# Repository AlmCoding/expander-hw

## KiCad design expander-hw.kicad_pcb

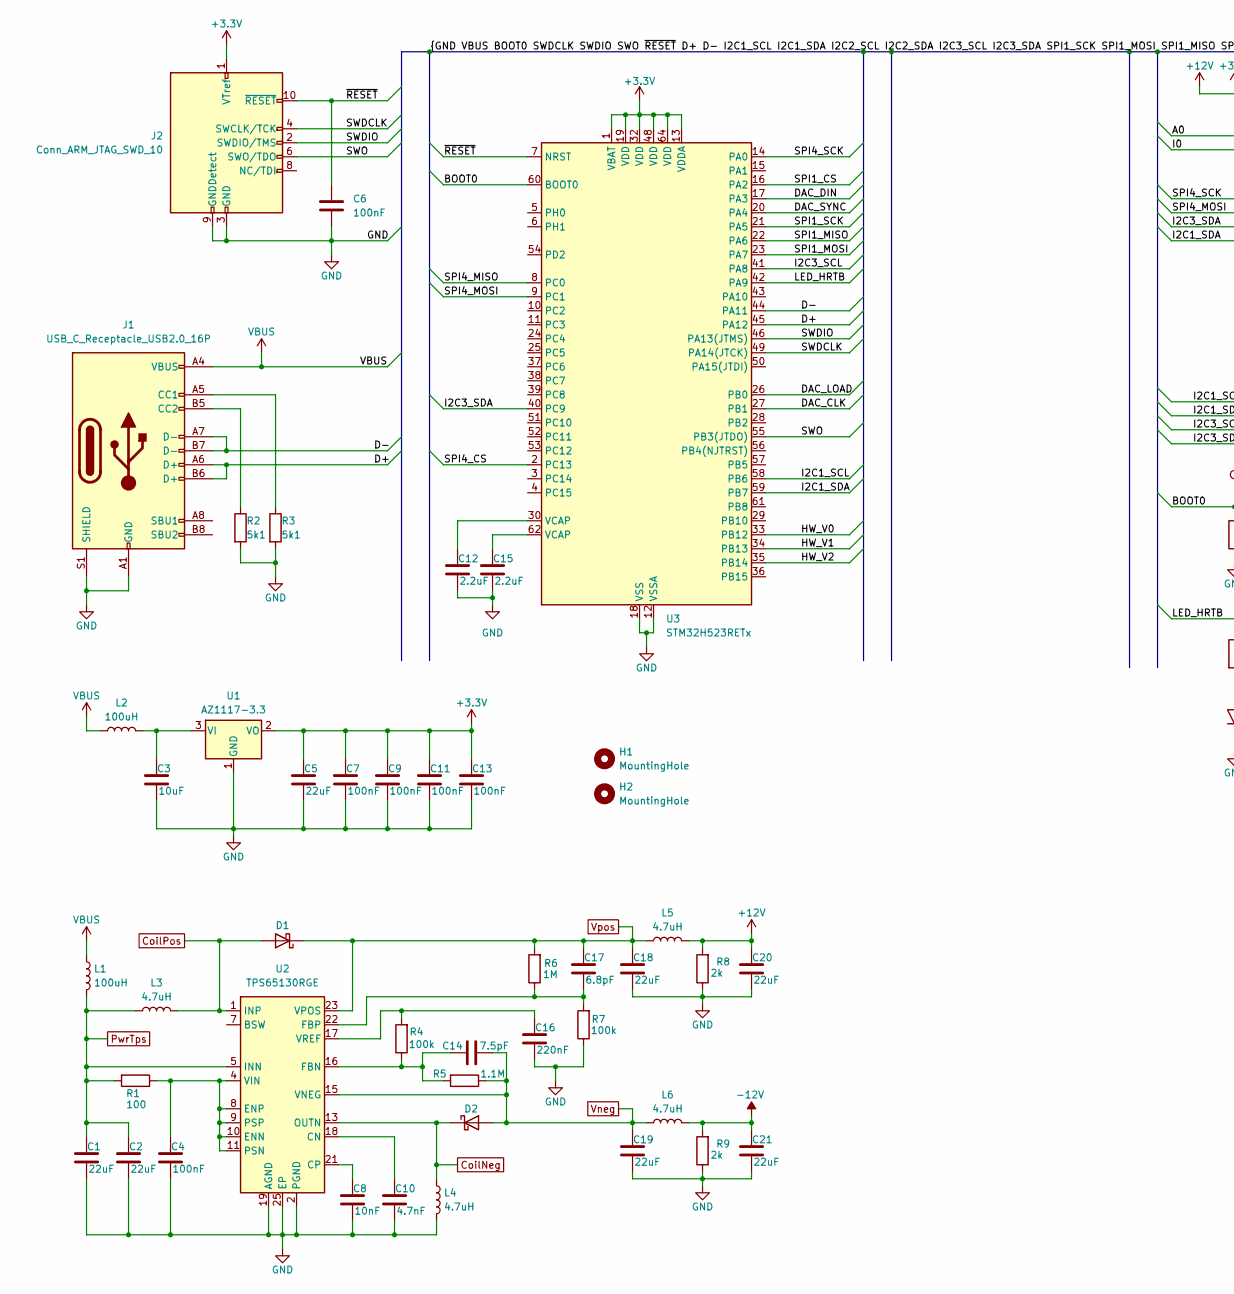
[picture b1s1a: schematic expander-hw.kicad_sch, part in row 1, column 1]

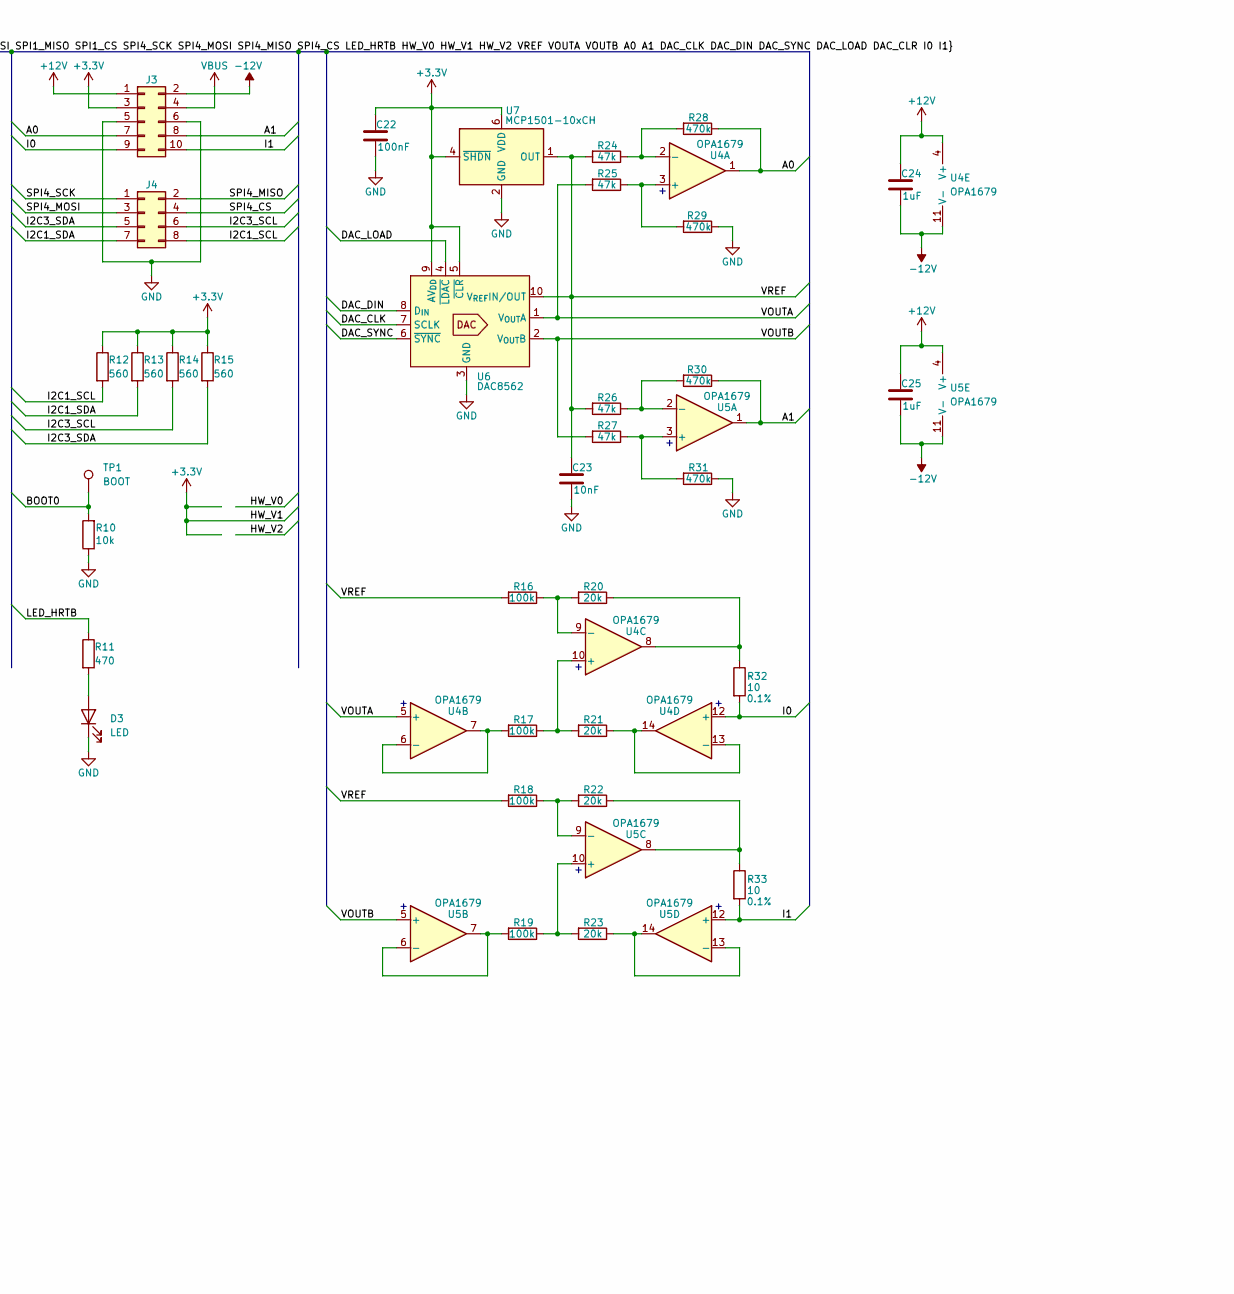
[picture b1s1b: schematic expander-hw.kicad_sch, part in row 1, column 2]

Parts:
C1, C2, C5, C18, C19, C20, C21: 22uF; C_0805_2012Metric
C3: 10uF; C_0805_2012Metric
C4, C6, C7, C9, C11, C13, C22: 100nF; C_0603_1608Metric
C8, C23: 10nF; C_0603_1608Metric
C10: 4.7nF; C_0603_1608Metric
C12, C15: 2.2uF; C_0603_1608Metric
C14: 7.5pF; C_0603_1608Metric
C16: 220nF; C_0603_1608Metric
C17: 6.8pF; C_0603_1608Metric
C24, C25: 1uF; C_0603_1608Metric
D1, D2: D_Schottky; D_0805_2012Metric
D3: LED; LED_0603_1608Metric
H1, H2: MountingHole; MountingHole_3.2mm_M3
J1: USB_C_Receptacle_USB2.0_16P; USB_C_Receptacle_G-Switch_GT-USB-7010ASV
J2: Conn_ARM_JTAG_SWD_10; PinHeader_2x05_P1.27mm_Vertical
J3: Conn_02x05_Odd_Even; PinHeader_2x05_P2.54mm_Horizontal
J4: Conn_02x04_Odd_Even; PinHeader_2x04_P2.54mm_Horizontal
L1, L2: 100uH; L_1210_3225Metric
L3, L4, L5, L6: 4.7uH; L_1210_3225Metric
R1: 100; R_0603_1608Metric
R2, R3: 5k1; R_0603_1608Metric
R4, R7, R16, R17, R18, R19: 100k; R_0603_1608Metric
R5: 1.1M; R_0603_1608Metric
R6: 1M; R_0603_1608Metric
R8, R9: 2k; R_0805_2012Metric
R10: 10k; R_0603_1608Metric
R11: 470; R_0603_1608Metric
R12, R13, R14, R15: 560; R_0603_1608Metric
R20, R21, R22, R23: 20k; R_0603_1608Metric
R24, R25, R26, R27: 47k; R_0603_1608Metric
R28, R29, R30, R31: 470k; R_0603_1608Metric
R32, R33: 10; R_0603_1608Metric; Tolerance 0.1%
TP1: BOOT; TestPoint_Pad_D2.5mm
U1: AZ1117-3.3; SOT-223-3_TabPin2
U2: TPS65130RGE; VQFN-24-1EP_4x4mm_P0.5mm_EP2.45x2.45mm_ThermalVias
U3: STM32H523RETx; LQFP-64_10x10mm_P0.5mm
U4, U5: OPA1679; SOIC-14_3.9x8.7mm_P1.27mm
U6: DAC8562; VSSOP-10_3x3mm_P0.5mm
U7: MCP1501-10xCH; SOT-23-6

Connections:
+3.3V: C5.1, C7.1, C9.1, C11.1, C13.1, C22.1, J2.1 (VTref), J3.3, R12.1, R13.1, R14.1, R15.1, U1.2 (VO), U3.1 (VBAT), U3.13 (VDDA), U3.19 (VDD), U3.32 (VDD), U3.34 (PB13), U3.48 (VDD), U3.64 (VDD), U6.5 (~CLR), U6.9 (AV_{DD}), U7.4 (~SHDN), U7.6 (VDD)
+12V: C20.1, C24.1, C25.1, J3.1, L5.2, R8.2, U4.4 (V+), U5.4 (V+)
-12V: C21.1, C24.2, C25.2, J3.2, L6.2, R9.2, U4.11 (V-), U5.11 (V-)
/A0: J3.7, R28.1, U4.1
/A1: J3.8, R30.1, U5.1
/BOOT0: R10.2, TP1.1, U3.60 (BOOT0)
/D+: J1.A6 (D+), J1.B6 (D+), U3.45 (PA12)
/D-: J1.A7 (D-), J1.B7 (D-), U3.44 (PA11)
/DAC_CLK: U3.27 (PB1), U6.7 (SCLK)
/DAC_DIN: U3.17 (PA3), U6.8 (D_{IN})
/DAC_LOAD: U3.26 (PB0), U6.4 (~LDAC)
/DAC_SYNC: U3.20 (PA4), U6.6 (~SYNC)
/HW_V0: U3.33 (PB12)
/HW_V2: U3.35 (PB14)
/I0: J3.9, R32.2, U4.12 (+)
/I1: J3.10, R33.2, U5.12 (+)
/I2C1_SCL: J4.8, R12.2, U3.58 (PB6)
/I2C1_SDA: J4.7, R13.2, U3.59 (PB7)
/I2C3_SCL: J4.6, R14.2, U3.41 (PA8)
/I2C3_SDA: J4.5, R15.2, U3.40 (PC9)
/LED_HRTB: R11.1, U3.42 (PA9)
/SPI1_CS: U3.16 (PA2)
/SPI1_MISO: U3.22 (PA6)
/SPI1_MOSI: U3.23 (PA7)
/SPI1_SCK: U3.21 (PA5)
/SPI4_CS: J4.4, U3.2 (PC13)
/SPI4_MISO: J4.2, U3.8 (PC0)
/SPI4_MOSI: J4.3, U3.9 (PC1)
/SPI4_SCK: J4.1, U3.14 (PA0)
/SWDCLK: J2.4 (SWCLK/TCK), U3.49 (PA14(JTCK))
/SWDIO: J2.2 (SWDIO/TMS), U3.46 (PA13(JTMS))
/SWO: J2.6 (SWO/TDO), U3.55 (PB3(JTDO))
/VOUTA: R25.2, U4.5 (+), U6.1 (V_{OUT}A)
/VOUTB: R27.2, U5.5 (+), U6.2 (V_{OUT}B)
/VREF: C23.1, R16.2, R18.2, R24.2, R26.2, U6.10 (V_{REF}IN/OUT), U7.1 (OUT)
/~RESET: C6.1, J2.10 (~RESET), U3.7 (NRST)
CoilNeg: D2.1 (K), L4.1, U2.13 (OUTN), U2.14 (OUTN)
CoilPos: D1.2 (A), L3.2, U2.1 (INP), U2.24 (INP)
GND: C1.2, C2.2, C3.2, C4.2, C5.2, C6.2, C7.2, C8.2, C9.2, C10.2, C11.2, C12.2, C13.2, C15.2, C16.2, C18.2, C19.2, C20.2, C21.2, C22.2, C23.2, D3.1 (K), J1.A1 (GND), J1.A12 (GND), J1.B1 (GND), J1.B12 (GND), J1.S1 (SHIELD), J2.3 (GND), J2.5 (GND), J2.9 (GNDDetect), J3.5, J3.6, L4.2, R2.2, R3.2, R7.1, R8.1, R9.1, R10.1, R29.1, R31.1, U1.1 (GND), U2.2 (PGND), U2.3 (PGND), U2.19 (AGND), U2.25 (EP), U3.12 (VSSA), U3.18 (VSS), U3.31 (VSS), U3.47 (VSS), U3.63 (VSS), U6.3 (GND), U7.2 (GND), U7.3 (GND), U7.5 (GND)
unnamed: C12.1, U3.30 (VCAP)
unnamed: C15.1, U3.62 (VCAP)
unnamed: D3.2 (A), R11.2
unnamed: J1.A5 (CC1), R3.1
unnamed: J1.B5 (CC2), R2.1
unnamed: R20.1, R32.1, U4.8
unnamed: R22.1, R33.1, U5.8
unnamed: C3.1, L2.2, U1.3 (VI)
unnamed: C10.1, U2.18 (CN)
unnamed: C8.1, U2.21 (CP)
unnamed: C4.1, R1.1, U2.4 (VIN), U2.8 (ENP), U2.9 (PSP), U2.10 (ENN), U2.11 (PSN)
unnamed: C14.1, R4.1, R5.2, U2.16 (FBN)
unnamed: C17.2, R6.1, R7.2, U2.22 (FBP)
unnamed: C16.1, R4.2, U2.17 (VREF)
unnamed: R25.1, R29.2, U4.3 (+)
unnamed: R24.1, R28.2, U4.2 (-)
unnamed: R17.2, U4.6 (-), U4.7
unnamed: R17.1, R21.2, U4.10 (+)
unnamed: R16.1, R20.2, U4.9 (-)
unnamed: R21.1, U4.13 (-), U4.14
unnamed: R27.1, R31.2, U5.3 (+)
unnamed: R26.1, R30.2, U5.2 (-)
unnamed: R19.2, U5.6 (-), U5.7
unnamed: R19.1, R23.2, U5.10 (+)
unnamed: R18.1, R22.2, U5.9 (-)
unnamed: R23.1, U5.13 (-), U5.14
PwrTps: C1.1, C2.1, L1.2, L3.1, R1.2, U2.5 (INN), U2.6 (INN)
VBUS: J1.A4 (VBUS), J1.A9 (VBUS), J1.B4 (VBUS), J1.B9 (VBUS), J3.4, L1.1, L2.1
Vneg: C14.2, C19.1, D2.2 (A), L6.1, R5.1, U2.15 (VNEG)
Vpos: C17.1, C18.1, D1.1 (K), L5.1, R6.2, U2.23 (VPOS)

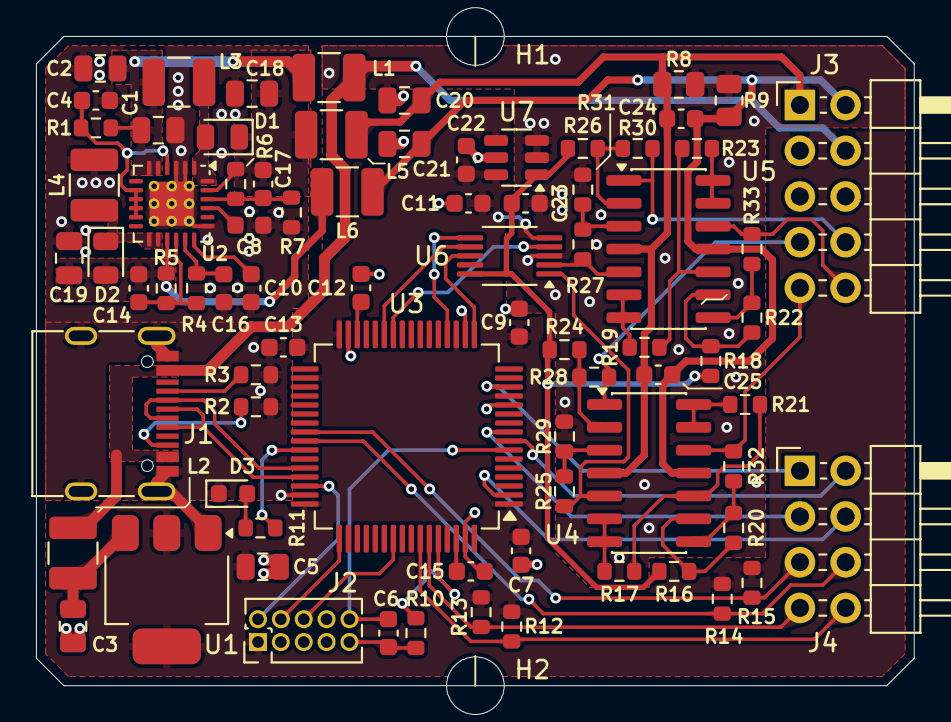
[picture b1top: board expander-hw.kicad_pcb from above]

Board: 2 copper layers, 48.8 x 36.1 mm, 81 parts (1 on the bottom side), 63 nets.

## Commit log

2024-03-14 Init project
2024-03-20 save
2024-03-24 Complete v1
2024-04-02 Add LED
2024-04-02 Fix vreg package
2024-04-10 Fix USB lines
2024-04-20 Move to STM32U545
2024-05-07 Fix SMPS, remove XTAL
2024-07-06 Add HW version + boot test point + SWD tag connector
2024-08-14 Switch to stm32h523 mcu
2024-10-03 Minor esthetical improvements
2024-12-11 Fix stm32h523 pinout
2024-12-15 Cleanup
2024-12-21 Move boot pin to back and add tear drops
2025-01-19 Increase boot pad size
2025-07-08 Migrate to KiCad version 9.0.0
2025-07-18 Add DAC hardware
2025-08-12 Fix boost converter + vref
2025-08-14 Refactor dac gain
2025-09-09 Small aesthetic changes
2025-09-19 Minor refactoring
2025-09-25 Fix converter EMI
2025-10-01 Remove Vref divider
2025-10-09 Add current converter
2025-10-20 Fix current converter
2025-11-03 Layout optimizations
2025-11-04 Improve Howland current pump
2025-11-22 Fix current pump interference
